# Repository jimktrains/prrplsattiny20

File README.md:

PRR Position Light Signals based on an ATTiny20
-----------------------------------------------
Thumb for scale.

In Action!

The Pennsylvania Railroad (PRR), almost uniquely among railroads, used
Position Light Signals (PLS) 
[[1]](https://en.wikipedia.org/wiki/North_American_railroad_signals#Position_light_signals)
[[2]](https://railroadsignals.us/signals/pl/pl.htm). (The Norfolk & Western
used Colored Position Lights (CPL) 
[[2]]([https://railroadsignals.us/signals/pl/pl.htm) which were similar.)

I model [N-Scale](https://en.wikipedia.org/wiki/N_scale) which is 1:160
scale. From scans of PRR plans
[[3]](http://prr.railfan.net/signalstandards/standards.cgi?plan=S-401-D&frame=YES&sortdir=up&sortby=1&rr=all)
the diameter of the signal is 4'4", which becomes 0.325" (8.255mm) for the
scale model.

I've designed the system to use 3 wires: +5V, Ground, and Serial. Serial
data comes in, the first command extracted, and then the remainder of a packet
is retransmitted similar to how WS2812b / NeoPixels work. 

Protocol
========

The serial protocol is 
[Differential Manchester](https://en.m.wikipedia.org/wiki/Differential_Manchester_encoding)
, but kind of overlaid on
a double-baud UART frame, so it always starts with the "0" stop bit.

I moved to this from just a plain software UART as the timing on some of my
signals was off by a large enough amount to throw everything out of sync.
Decoding the differential Manchester packet is much less timing-sensitive.
It runs at 300baud/150bps with 4-bit packets.

A packet starts with an 0x4 followed a sequence of 0x3 for Stop, 0x2 for
Approach, and 0x1 for Clear, 0x0 for all lights off.

In this example, the controller sends out a 4-frame packet. Starting with a SOP (Start of Packet) frame, followed
by an Approach, then Stop, then All Off. The first signal dutifully forwards
the SOP frame. The second frame is for it, though, so it does not forward 
that one. The rest of the frames are for subsequent signals, so it forwards
all subsequent frames until a SOP is encountered again. The second signal
does as the first. It forwards the SOP, keeps the frame following the SOP,
and forwards any remaining frames until another SOP is encountered.

Also, note how when interpreted as a UART, the packets coming from the signals
isn't in sync with the baudrate. I'm sure that there's some way to get a more
stable clock on the μC, but it was significantly easier for me to switch to a
more forgiving line coding. 

There also needs to be at least a 20 symbol pause between frames sent. I 
think this has to do with how I decode the frame, but it deserves to be
looked at.

(The visualization is from PulseView/sigrok. I wrote a custom protocol
decoder to help me debug.)

Schematics / PCB
================

### General Notes

I am using an 
[ATTiny20](https://ww1.microchip.com/downloads/en/DeviceDoc/Atmel-8235-8-bit-AVR-Microcontroller-ATtiny20_Datasheet.pdf)
in a 
[WLCSP](https://en.wikipedia.org/wiki/Wafer-level_packaging) package 
(1.56mm&times;1.4mm) with 0.4mm balls, and I'm not sure I can solder that
at my current skill level.) I'm just bemused at it's physical size, even if
it only has 128 bytes of RAM. It fits perfectly in the area available,
allows for components on a single side, and has enough I/O to control
the LEDs individually.

In order to avoid having to place a resistor per
LED, I'm using the pull-up resistors in the microcontroller. Since these
are large-resistance resistors, it limits the brightness of the LEDs. While
the pull-up resistors aren't any specific resistance and can be pretty
variable, the ones within a single chip should be pretty similar. This may
mean that signals visibility near each other may be of different brightness,
but so far it doesn't appear to be a noticeable issue.

The limited brightness is a potential problem, but I'm going to try up the
effective PWM duty cycle. If each light is updated sequentially at the
frequency at which the RX pin is sampled spread over the 7 lights -- 
currently 1200Hz with a 1/7 (14%) duty cycle. Because the LEDs are
charliplexed I am limited in which LEDs I could turn on simultaneously.
However, because I separated out the center light and I think lucked into
arranging the lights in a sensible order I am able to have them on with
100% duty cycle for the 3 basic aspects these display (Stop, Clear, and
Approach). For those aspects I think the current brightness is adequate.

### PCB Notes

The PCB design is fairly simple, and using 4 layers (Signal, +5V+Minimal Signal,
GND, Signal) made routing easier.

To avoid using via-in-pads (and being charged accordingly), there are 3 pins
(balls?) that aren't used. If they had been used, each LED could have been
directly connected to the μC. As such, I was able to control the LEDs
individually by charlieplexing them.

I used a 1.27mm pitch SOIC chip clip as my connectorless connector. (I did
manage to make the through-holes a little too small, so it doesn't attach
as securely as I would have liked.) Eventually I just soldered some THT
resistor legs to these to connect to a breadboard for some of the signal
heads.

When panalized, I added some traces that I can use to interconnect columns
for testing.

### Individual Schematic

### Front Copper

### Inner 1 Copper

### Inner 2 Copper

### Back Copper

Programming and Testing
========================

Here is how I test and program these modules. The Arduino is running [this
sketch](tpi_programmer/) from [Junk +
Arduino](https://junkplusarduino.blogspot.com/p/attiny10-resources.html). I
added a software serial console to it to make testing easier. The FT232RL in
the schematic is actually a breakout board that provides the +5V.

My next step is to use 38 gauge (40mil (0.1007mm) diameter) enameled wire to
wire the signals into a wayside signal on a post, and then a signal bridge.

Please excuse my soldering. This is back of what was in the video above.
Just a proof of concept that the enamel wire will work. (Well, more that
I can make it work, e.g. strip it without breaking it and soldering it.)

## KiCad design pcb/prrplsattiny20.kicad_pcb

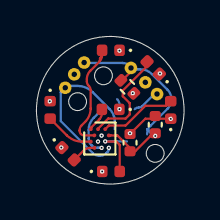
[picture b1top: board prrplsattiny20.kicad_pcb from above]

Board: 4 copper layers, 8.2 x 8.2 mm, 18 parts (1 on the bottom side), 12 nets.

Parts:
C1: 100nF; C_0402_1005Metric
C1001: 22μF; C_0402_1005Metric
D1, D2, D3, D4, D5, D6, D7: YELLOW LED; LED_0402_1005Metric
J1: Conn_02x08_Counter_Clockwise; Tag-Connect_TC2030-IDC-NL_2x03_P1.27mm_Vertical
J1001, J1002, J1003, J1004, J1005, J1006: Conn_01x01; SolderWire-D0.7mm_Drill0.3
R1: 1M; R_0402_1005Metric
U1: ATtiny20-UUR; WLCSP-12_1.403x1.555mm_Layout6x4_P0.4mm_Stagger

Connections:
+5V: C1.1, C1001.1, J1.2, J1002.1, J1004.1, R1.2, U1.B6 (VCC)
/A1: D4.2 (A), U1.A1 (PA4)
/A3: D2.2 (A), U1.A3 (PA1)
/A5: D5.2 (A), U1.A5 (PA2)
/B2: D1.2 (A), U1.B2 (PA6)
/C1: D3.2 (A), U1.C1 (PA5)
/D2: D6.2 (A), U1.D2 (PB2)
/Serial_In: J1.4, J1003.1, U1.C3 (PA7)
/TPICLK_SO: J1.3, J1001.1, U1.D6 (PB0)
/TPIDATA: D7.2 (A), J1.1, U1.C5 (PB1)
/~RESET: J1.5, R1.1, U1.D4 (~RESET/PB3)
GND: C1.2, C1001.2, D1.1 (K), D2.1 (K), D3.1 (K), D4.1 (K), D5.1 (K), D6.1 (K), D7.1 (K), J1.6, J1005.1, J1006.1, U1.B4 (GND)

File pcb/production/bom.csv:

Designator,Footprint,Quantity,Value,LCSC Part #
"C1_25, C1_24, C1_23, C1_22, C1_21, C1_20, C1_19, C1_18, C1_17, C1_16, C1_15, C1_14, C1_13, C1_12, C1_11, C1_10, C1_9, C1_8, C1_7, C1_6, C1_5, C1_4, C1_3, C1_2, C1",0402,25,100nF,C22435938
"C1001_25, C1001_24, C1001_23, C1001_22, C1001_21, C1001_20, C1001_19, C1001_18, C1001_17, C1001_16, C1001_15, C1001_14, C1001_13, C1001_12, C1001_11, C1001_10, C1001_9, C1001_8, C1001_7, C1001_6, C1001_5, C1001_4, C1001_3, C1001_2, C1001",0402,25,22μF,
"D1_25, D1_24, D1_23, D1_22, D1_21, D1_20, D1_19, D1_18, D1_17, D1_16, D1_15, D1_14, D1_13, D1_12, D1_11, D1_10, D1_9, D1_8, D1_7, D1_6, D1_5, D1_4, D1_3, D1_2, D1, D2_25, D2_24, D2_23, D2_22, D2_21, D2_20, D2_19, D2_18, D2_17, D2_16, D2_15, D2_14, D2_13, D2_12, D2_11, D2_10, D2_9, D2_8, D2_7, D2_6, D2_5, D2_4, D2_3, D2_2, D2, D3_25, D3_24, D3_23, D3_22, D3_21, D3_20, D3_19, D3_18, D3_17, D3_16, D3_15, D3_14, D3_13, D3_12, D3_11, D3_10, D3_9, D3_8, D3_7, D3_6, D3_5, D3_4, D3_3, D3_2, D3, D4_25, D4_24, D4_23, D4_22, D4_21, D4_20, D4_19, D4_18, D4_17, D4_16, D4_15, D4_14, D4_13, D4_12, D4_11, D4_10, D4_9, D4_8, D4_7, D4_6, D4_5, D4_4, D4_3, D4_2, D4, D5_25, D5_24, D5_23, D5_22, D5_21, D5_20, D5_19, D5_18, D5_17, D5_16, D5_15, D5_14, D5_13, D5_12, D5_11, D5_10, D5_9, D5_8, D5_7, D5_6, D5_5, D5_4, D5_3, D5_2, D5, D6_25, D6_24, D6_23, D6_22, D6_21, D6_20, D6_19, D6_18, D6_17, D6_16, D6_15, D6_14, D6_13, D6_12, D6_11, D6_10, D6_9, D6_8, D6_7, D6_6, D6_5, D6_4, D6_3, D6_2, D6, D7_25, D7_24, D7_23, D7_22, D7_21, D7_20, D7_19, D7_18, D7_17, D7_16, D7_15, D7_14, D7_13, D7_12, D7_11, D7_10, D7_9, D7_8, D7_7, D7_6, D7_5, D7_4, D7_3, D7_2, D7",0402,175,YELLOW LED,C779450
"J1_25, J1_24, J1_23, J1_22, J1_21, J1_20, J1_19, J1_18, J1_17, J1_16, J1_15, J1_14, J1_13, J1_12, J1_11, J1_10, J1_9, J1_8, J1_7, J1_6, J1_5, J1_4, J1_3, J1_2, J1",Tag-Connect_TC2030-IDC-NL_2x03_P1.27mm_Vertical,25,Conn_02x08_Counter_Clockwise,
"J1001_25, J1001_24, J1001_23, J1001_22, J1001_21, J1001_20, J1001_19, J1001_18, J1001_17, J1001_16, J1001_15, J1001_14, J1001_13, J1001_12, J1001_11, J1001_10, J1001_9, J1001_8, J1001_7, J1001_6, J1001_5, J1001_4, J1001_3, J1001_2, J1001, J1002_25, J1002_24, J1002_23, J1002_22, J1002_21, J1002_20, J1002_19, J1002_18, J1002_17, J1002_16, J1002_15, J1002_14, J1002_13, J1002_12, J1002_11, J1002_10, J1002_9, J1002_8, J1002_7, J1002_6, J1002_5, J1002_4, J1002_3, J1002_2, J1002, J1003_25, J1003_24, J1003_23, J1003_22, J1003_21, J1003_20, J1003_19, J1003_18, J1003_17, J1003_16, J1003_15, J1003_14, J1003_13, J1003_12, J1003_11, J1003_10, J1003_9, J1003_8, J1003_7, J1003_6, J1003_5, J1003_4, J1003_3, J1003_2, J1003, J1004_25, J1004_24, J1004_23, J1004_22, J1004_21, J1004_20, J1004_19, J1004_18, J1004_17, J1004_16, J1004_15, J1004_14, J1004_13, J1004_12, J1004_11, J1004_10, J1004_9, J1004_8, J1004_7, J1004_6, J1004_5, J1004_4, J1004_3, J1004_2, J1004, J1005_25, J1005_24, J1005_23, J1005_22, J1005_21, J1005_20, J1005_19, J1005_18, J1005_17, J1005_16, J1005_15, J1005_14, J1005_13, J1005_12, J1005_11, J1005_10, J1005_9, J1005_8, J1005_7, J1005_6, J1005_5, J1005_4, J1005_3, J1005_2, J1005, J1006_25, J1006_24, J1006_23, J1006_22, J1006_21, J1006_20, J1006_19, J1006_18, J1006_17, J1006_16, J1006_15, J1006_14, J1006_13, J1006_12, J1006_11, J1006_10, J1006_9, J1006_8, J1006_7, J1006_6, J1006_5, J1006_4, J1006_3, J1006_2, J1006",SolderWire-D0.7mm_Drill0.3,150,Conn_01x01,
"R1_25, R1_24, R1_23, R1_22, R1_21, R1_20, R1_19, R1_18, R1_17, R1_16, R1_15, R1_14, R1_13, R1_12, R1_11, R1_10, R1_9, R1_8, R1_7, R1_6, R1_5, R1_4, R1_3, R1_2, R1",0402,25,1M,C138033
"U1_25, U1_24, U1_23, U1_22, U1_21, U1_20, U1_19, U1_18, U1_17, U1_16, U1_15, U1_14, U1_13, U1_12, U1_11, U1_10, U1_9, U1_8, U1_7, U1_6, U1_5, U1_4, U1_3, U1_2, U1",WLCSP-12_1.403x1.555mm_Layout6x4_P0.4mm_Stagger,25,ATtiny20-UUR,C219130

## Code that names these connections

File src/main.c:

/*
 * Copyright 2025 jsk AGPL3
 *
 * File:   main.c
 * Author: jim
 *
 * Created on July 8, 2025, 1:19 AM
 */

#include <avr/interrupt.h>
#include <avr/io.h>
#include <avr/pgmspace.h>
#include <stdint.h>

#define SOFT_BAUD 300
#define RX_PIN PB0
#define TX_PIN PB1
#include "./soft_uart.h"


#define EP_A PA5
#define EP_B PA6
#define EP_C PB2
#define EP_CENTER PA4

#define EP_A_FLAG (1 << EP_A)
#define EP_B_FLAG (1 << EP_B)
#define EP_C_FLAG (1 << EP_C)
#define EP_CENTER_FLAG (1 << EP_CENTER)

#define EP_PORTA (EP_A_FLAG | EP_B_FLAG | EP_CENTER_FLAG)
#define EP_PORTB (EP_C_FLAG)

/*
 * LEDs are connected to PA5, PA6, and PB2.
 * Center LED is PA4 connected to ground at the cathode.
 * Use the internal pull up resistors to power them.
 */
#define STOP_1 0x65
#define STOP_2 0x25
#define APPR_1 0x62
#define APPR_2 0x52
#define CLEAR_1 0x26
#define CLEAR_2 0x56
#define CENTER 0x40
#define ALLOFF 0x00

#define STOP_1_BIT 0
#define STOP_2_BIT 1
#define APPR_1_BIT 2
#define APPR_2_BIT 3
#define CLEAR_1_BIT 4
#define CLEAR_2_BIT 5
#define CENTER_BIT 6

#define STOP_1_FLAG (1 << STOP_1_BIT)
#define STOP_2_FLAG (1 << STOP_2_BIT)
#define APPR_1_FLAG (1 << APPR_1_BIT)
#define APPR_2_FLAG (1 << APPR_2_BIT)
#define CLEAR_1_FLAG (1 << CLEAR_1_BIT)
#define CLEAR_2_FLAG (1 << CLEAR_2_BIT)
#define CENTER_FLAG (1 << CENTER_BIT)

#define STOP_ASP (STOP_1_FLAG | STOP_2_FLAG | CENTER_FLAG)
#define APPR_ASP (APPR_1_FLAG | APPR_2_FLAG | CENTER_FLAG)
#define CLEAR_ASP (CLEAR_1_FLAG | CLEAR_2_FLAG | CENTER_FLAG)

const uint8_t PROGMEM lightidx[7] = {STOP_1, STOP_2, APPR_1, APPR_2,
                                     CLEAR_1,  CLEAR_2,  CENTER};
uint8_t lightson = ALLOFF;
uint8_t cur_light_bit = 6;

void light_led(uint8_t light) {
  uint8_t source = 0x0f & light;
  uint8_t sink = (0xf0 & light) >> 4;

  // Put All LEDs into z state
  // i.e. input with no pull-up
  PUEA &= ~EP_PORTA;
  PUEB &= ~EP_PORTB;
  DDRA &= ~EP_PORTA;
  DDRB &= ~EP_PORTB;

  PUEB |= (source == 2) << 2;
  PUEA |= (source != 2 && source != 0) << source;

  DDRB |= (sink == 2) << 2;
  DDRA |= (sink != 2 && sink != 0) << sink;
}

int main(void) {
  // Init LEDs Off
  light_led(ALLOFF);
  // Set the LED pins to be a sink/ground when set as output.
  PORTA &= ~EP_PORTA;
  PORTB &= ~EP_PORTB;

  setup_timer(SOFT_BAUD);

  // Set DDR for Rx and Tx Pins
  DDRB |= ((1 << RX_PIN) | (1 << TX_PIN));

  while (1) {
    // Check if timer output compare was set.
    if (TIFR & (1 << OCF0A)) {
      // Clear the compare match flag.
      TIFR |= (1 << OCF0A);

      if (cur_light_bit == 6) {
        cur_light_bit = 0;
      } else {
        cur_light_bit += 1;
      }
      if (lightson & (1 << cur_light_bit)) {
        light_led(lightidx[cur_light_bit]);
      }

      listen();
      send();

      if (new_next_to_tx && tx_ccount == 0) {
        new_next_to_tx = 0;
        new_tx = 1;
        tx_buf = next_to_tx;
      }
      if (new_last_recv) {
        new_last_recv = 0;
        // Our command is right after the packet start, so we don't
        // retransmit it.
        if (last_recv_packet_start) {
          last_recv_packet_start = 0;
          if (last_recv == 'S') {
            lightson = STOP_ASP;
          } else if (last_recv == 'A') {
            lightson = APPR_ASP;
          } else if (last_recv == 'C') {
            lightson = CLEAR_ASP;
          } else {
            lightson = ALLOFF;
          }
        } else {
          if (last_recv == '!') {
            last_recv_packet_start = 1;
          }
          new_next_to_tx = 1;
          next_to_tx = last_recv;
        }
      }
    }
  }
}

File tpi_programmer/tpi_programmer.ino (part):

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//
//    Arduino                ATtiny10
//    -----------+          +----------------
//    (SS#)  D10 |----------| 6 (RESET#/PB3)
//               |          |
//    (MOSI) D11 |--[R]--+--| 1 (TPIDATA/PB0)
//               |       |  |
//    (MISO) D12 |-------+  |
//               |          |
//    (SCK)  D13 |----------| 3 (TPICLK/PB1)
//    -----------+          +----------------
//
//    -----------+          +----------------
//    (HVP)   D9 |---       | 6 (RESET#/PB3)
//               |          |
//
//  -[R]-  =  2.2kΩ resistor
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
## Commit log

2025-07-15 init
2025-07-15 adding in the kicad pcb
2025-07-15 adding the agpl
2025-07-15 updating README
2025-07-15 mixed up my markdown links
2025-07-15 Adding to README
2025-07-15 I like links.
2025-07-15 adding the baud rate
2025-07-15 note about looping vs interrupt
2025-09-06 checkpoint
2025-09-23 first working version on the actual hardware!
2025-09-23 Updating the README
2025-09-23 Adding a note about the FTDI chip
2025-09-23 adding gifs instead of videos
2025-09-23 show not-connected in test circuit
2025-09-23 removing testcircuit empty dir
2025-09-23 removing links to old videos that are now gifs
2025-09-23 cleanup
2025-09-23 make the common aspects brighter
2025-09-23 adding schematics to README
2025-09-23 Fixing README
2025-09-23 Adding some notes
2025-09-26 switching to a differential manchester coding for the comms protocol
2025-09-26 adding sigrok decoders
2025-09-26 updating comments on the protocol example
2025-09-26 fix link in readme
2025-09-27 updating readme and video
2025-10-13 adding a keypad to change signals
2025-10-13 v2 of the pcb
2025-10-14 adding Wall and Wextra
2025-10-14 adding msg when resetting
2025-10-14 experimenting with a new async encoding
2025-10-14 adding noise to test
2025-10-14 better heuristic to guess bits

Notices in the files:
tpi_programmer/tpi_programmer.ino:
This code is expressly licensed under the MIT License.
